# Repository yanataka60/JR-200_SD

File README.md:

# National JR-200にSD-CARDとのロード、セーブ機能

　JR-200でSD-CARDからcjr形式ファイルのロード、セーブ機能を実現するものです。

　CMTからの読み込み実行に数分掛かっていたゲームも数十秒で実行できます。

　接続は、JR-200本体後ろの拡張端子からフラットケーブルで接続して使います。

　なお、Arduino、ROMへ書き込むための機器が別途必要となります。

### 2025.2.26 PIOに6821を使ったRev2.1ではPIOアクセス時の画面ノイズが発生しないので6821版を正式版とし、8255版は8255フォルダに移動しました。なお、開発に使用した2台のJR-200では6821版、8255版ともに安定動作していますが、8255版は動作不安定であると報告された機体でも6821版は安定動作しているとの動作報告がありました。

## 回路図
　KiCadフォルダ内のJR-200_SD.pdfを参照してください。

[回路図](https://github.com/yanataka60/JR-200_SD/blob/main/Kicad/JR-200_SD.pdf)

## 部品
|番号|品名|数量|備考|
| ------------ | ------------ | ------------ | ------------ |
|J1|2x25ボックスヘッダ|1|共立エレショップ JS-1200R-50など、秋月電子通商 PH-2x40RGなどのピンヘッダでも代用可(注1)|
||J2、J3のいずれか|||
|J2|Micro_SD_Card_Kit|1|秋月電子通商 AE-microSD-LLCNV (注2) (注3)|
|J3|MicroSD Card Adapter|1|Arduino等に使われる5V電源に対応したもの (注3)|
|S1、S2|3Pスライドスイッチ又はピンヘッダ、ジャンパーピン|2|秋月電子通商 SS12D01G4など|
|U1、U3、U6|74LS04|3||
|U2、U4、U7|74LS30|3||
|U5|ROM 2764/27256/27512相当品|1||
|U8|6821|1|若松通商 HD46821P等|
|U9|Arduino_Pro_Mini_5V|1|Atmega328版を使用 168版は不可。(注4)|
|C2-C9|積層セラミックコンデンサ 0.1uF|8||
|C1|電解コンデンサ 16v100uF|1||
||50Pinフラットケーブル|1||
||ピンヘッダ|2Pin分|Arduino_Pro_MiniにはA4、A5用のピンヘッダが付いていないため別途調達が必要です 秋月電子通商 PH-1x40SGなど|
||ピンソケット(任意)|26Pin分|Arduino_Pro_Miniを取り外し可能としたい場合に調達します 秋月電子通商 FHU-1x42SGなど|

　　　注1)ピンヘッダで代用するときは、基板から若干浮かせてピンヘッダをハンダ付けするとフラットケーブをスムーズに抜き差しできます。

　　　注2)秋月電子通商　AE-microSD-LLCNVのJ1ジャンパはショートしてください。

　　　注3)J2又はJ3のどちらかを選択して取り付けてください。

### 　　注4)Arduino Pro MiniはA4、A5ピンも使っています。

### MicroSD Card Adapterを使う
　J3に取り付けます。

　MicroSD Card Adapterについているピンヘッダを除去してハンダ付けするのが一番確実ですが、J3の穴にMicroSD Card Adapterをぴったりと押しつけ、裏から多めにハンダを流し込むことでハンダ付けをする方法もあります。なお、この方法の時にはしっかりハンダ付けが出来たかテスターで導通を確認しておいた方が安心です。

　ハンダ付けに自信のない方はJ2の秋月電子通商　AE-microSD-LLCNVをお使いください。AE-microSD-LLCNVならパワーLED、アクセスLEDが付いています。

## ROMへの書込み
　ROMフォルダ内のSD.binをROMライター(TL866II Plus等)を使って2764、27256又は27512に書き込みます。

### ROMの相性
　開発中にAT28C64 15PCを使ったところ、正常に動作しないという現象がありました。

　AT28C64 15PCよりアクセスタイムが遅いROMを使用しても問題が発生しないため、単純にアクセスタイムの早いROMを使えばよいと言う訳でもないようです。

　入手性を鑑み、2764、27256、27512互換ROMを使えるようにしてあります。
#### 問題なし
|メーカー|品名|
| ------ | -- |
|ATMEL|AT28C64B-15PC|
|NEC|D27512J-2|
|ST|M2764A-25F1|
|ST|M27256-2F1|
|ST|M27C512-10F1|
|TOSHIBA|TMM2764D|
|TOSHIBA|TMM2764AD-20|
|Winbond|W27C512-45Z|

#### 問題あり
|メーカー|品名|備考|
| ------ | -- | -- |
|ATMEL|AT28C64-15PC|ほぼ誤動作|
|ATMEL|AT28C256-15PC|2764とはピン非互換|
|ATMEL|AT29C256-25PC|時々誤動作|

## Arduinoプログラム
　Arduino IDEを使ってArduinoフォルダのJR-200_SDフォルダ内JR-200.inoを書き込みます。

　SdFatライブラリを使用しているのでArduino IDEメニューのライブラリの管理からライブラリマネージャを立ち上げて「SdFat」をインストールしてください。

　「SdFat」で検索すれば見つかります。「SdFat」と「SdFat - Adafruit Fork」が見つかりますが「SdFat」のほうを使っています。

注)Arduinoを基板に直付けしている場合、Arduinoプログラムを書き込むときは、JR-200本体とは接続を外したうえで書き込んでください。

## 接続
　JR-200本体後ろの拡張端子からフラットケーブルで接続します。

.JPG)

#### 注)JR-200本体上面の塗装の下には伝導性の塗装(?)があるようで剥げかけている個所に接触するとショートの可能性があります。基板を本体上面に置くときには基板下面が本体と接触しないよう絶縁してください。

## SD-CARD
　出来ればSD規格のSDカードを用意してください。

　ArduinoのSdFatライブラリは、SD規格(最大2GB)、SDHC規格(2GB～32GB)に対応していますが、SDXC規格(32GB～2TB)には対応していません。

　また、SDHC規格のSDカードであっても相性により動作しないものがあるようです。

　FAT16又はFAT32が認識できます。NTFSは認識できません。

　ルートに置かれた拡張子が「.CJR」のCJR形式ファイルのみ認識できます。(CJR形式以外のファイル、フォルダも表示されますがLOADの対象になりません)

　ファイル名は「.CJR」を含めて31文字まで、ただし半角カタカナ、及び一部の記号はArduinoが認識しないので使えません。パソコンでファイル名を付けるときはアルファベット、数字および空白でファイル名をつけてください。

## CJR形式
　複数セクションが含まれるCJRファイルは読み込ませないでください。最初のセクションの読込が終了した後、Arduinoは次のセクションを送出しようとして待機状態となり、電源を入れ直すか、RESETするまで正常に動作しなくなります。

## 動作環境
　現在5.00と5.01での動作を確認しています。

## 使い方

### Launcherの起動
　MONコマンドでモニタに入り、G8000[CR]でLauncherが起動します。(Gは大文字)

　注)BASICからa=usr($8000)でも起動出来ますが、BASICプログラムをロードした後は、!コマンドで戻らずにBREAKキーで戻ってください。!コマンドで戻るとBASICプログラムが壊れます。

　コマンドプロンプトが「>」から「SD>」に変わり以下のコマンドが使えるようになります。

　~SDへのアクセス中に画面にノイズが出ますが、異常ではありません。ノイズが出ないようにする方法が不明なためそのままにしてあります。~(2025.2.20 PIOを6821にすることで解消されました。)

#### SDDIR[CR]又はSDDIR "文字列"[CR]
　SDDIR[CR]とするとSD-CARDルートディレクトリにあるファイルの一覧を表示します。

　SDDIR "文字列"[CR]とするとSD-CARDルートディレクトリにあるその文字列から始まるファイルの一覧を表示します。ダブルコーテーションはあっても無くても構いません。

　10件表示したところで指示待ちになるので打ち切るならRETURNを入力すると打ち切られ、Bキーで前の10件に戻ります。それ以外のキーで次の10件を表示します。

　LOADしたいファイルを見つけたら左端の数字のキーを押せばLOADされます。

　BASICプログラムか、機械語プログラムかは自動で判断します。

　表示される順番は、登録順となりファイル名アルファベッド順などのソートした順で表示することはできません。

#### LOAD "DOSファイル名"[CR]
　指定したDOSフィル名のプログラムをSD-CARDからLOADします。ダブルコーテーションはあっても無くても構いません。

　BASICプログラムか、機械語プログラムかは自動で判断し、どちらをLOADしているかメッセージに表示します。

　また、機械語プログラムのLOAD時には読み込み開始アドレス、読み込み終了アドレスも表示されます。

　ファイル名の最後の「.CJR」は有っても無くても構いません。

　例)

　　LOAD "TEST" -> DOSファイル名「TEST.CJR」を読み込みます。

　　LOAD "TEST.BAS" -> DOSファイル名「TEST.BAS.CJR」を読み込みます。

　　LOAD "TEST.BAS.CMT" -> DOSファイル名「TEST.BAS.CJR」を読み込みます。

#### MEXEC[CR]
　機械語プログラムをLOADした後、Gxxxx[CR]として機械語プログラムを実行する代わりに実行アドレスが読み込み開始アドレスと同じ場合にはMEXEC[CR]とすることで機械語プログラムを実行できます。

#### SAVE "DOSファイル名"[CR]
　BASICプログラムを指定したDOSフィル名でSD-CARDに上書きSAVEします。ダブルコーテーションはあっても無くても構いません。

　ファイル名の省略は出来ません。

　ファイル名の最後の「.CJR」は有っても無くても構いません。

　指定したDOSファイル名の最初の16文字がCJR形式の中に保存されるファイル名として使われます。

　BASICプログラムであることを識別するためDOSファイル名に「.BAS」を含ませることを推奨します。

　例)

　　SAVE "TEST" -> 「TEST.CJR」で保存される。

　　SAVE "TEST.BAS" -> 「TEST.BAS.CJR」で保存される。

#### MSAVE $xxxx,$yyyy,"DOSファイル名"[CR]
　16進数4桁で指定する$xxxxから$yyyyまでの機械語プログラムを指定したDOSフィル名でSD-CARDに上書きSAVEします。ダブルコーテーションはあっても無くても構いません。

　16進数4桁で指定するアドレスは$をつけてもつけなくても構いません。

　ファイル名の省略は出来ません。

　ファイル名の最後の「.CJR」は有っても無くても構いません。

　指定したDOSファイル名の最初の16文字がCJR形式の中に保存されるファイル名として使われます。

　機械語プログラムであることを識別するためDOSファイル名に「.BIN」を含ませることを推奨します。

　例)

　　MSAVE $E000,$FFFF,"TEST" -> 「TEST.CJR」で保存される。

　　MSAVE E000,FFFF,"TEST.BIN" -> 「TEST.BIN.CJR」で保存される。

#### G $xxxx[CR]
　16進数4桁で指定する$xxxxから始まるプログラムを実行します。

　16進数4桁で指定するアドレスは$をつけてもつけなくても構いません。

#### ![CR]
　JR-200のMONITORに戻ります。

　BASICからa=usr($8000)でLauncherを起動してBASICプログラムをロードした場合には、!コマンドでBASICに戻らないでください。BASICプログラムが破壊されます。

#### BREAKキー
　BASICに戻ります。

　JR-200のBREAKキーは割込み処理によりどんな時でもBASICに戻れるのですが、SDDIRを実行して10件表示したところで指示待ちの時には絶対に押さないでください。

　Arduinoが指示待ちのままになり、電源を再投入するか、リセットするまでSDは使えなくなります。

### BASICプログラム中から機械語プログラムをSDからLOADしたい場合
#### A=USR($8003):REM xxxxx
　A=USR($8003)の直後に書かれたREM文のコメント文字列(xxxxx)をファイル名として解釈してSDからLOADします。

　文字列をダブルコーテーションで括っても括らなくても構いません。また、事前にLauncherの起動も不要です。

　ただし、LOADするのは機械語プログラムのみにしてください。

　BASICプログラムをLOADするとBASICに復帰した時にBASICプログラムを破壊してしまい暴走します。(ダイレクトモードであっても破壊されます)

　例)

　　10 A=USR($8003):REM Demodata

## 操作上の注意
　SD-CARDにアクセスしていない時には電源が入ったままでもSD-CARDを抜くことが出来ます。

　再度SD-CARDを挿入した後、SDDIR、LOAD、SAVE等でSD-CARDに3回ほどアクセスすれば復旧します。

　ただし、SD-CARDの抜き差しは電源を切った状態で行うほうがより確実です。

## 謝辞
　基板の作成に当たり以下のデータを使わせていただきました。ありがとうございました。

　　Arduino Pro Mini

　　　https://github.com/g200kg/kicad-lib-arduino

　　AE-microSD-LLCNV

　　　https://github.com/kuninet/PC-8001-SD-8kRAM

## 追記
2025.1.27 部品に50Pinフラットケーブルを追加しました。

2025.1.29 コネクタの記述を修正しました。

2025.1.31 MSAVEのアドレス指定に$がついていた誤記を訂正しました。

2025.1.31 MSAVEのアドレス指定に$をつけてもつけなくてもよいことに修正。Gコマンドの記述が抜けていたので追加。JR-200_SD設置時の注意を追記。

2025.2.3 動作が不安定な時があるとの動作報告があったことを追記。

2025.2.20 PIOに6821を採用した6821版に移行した。

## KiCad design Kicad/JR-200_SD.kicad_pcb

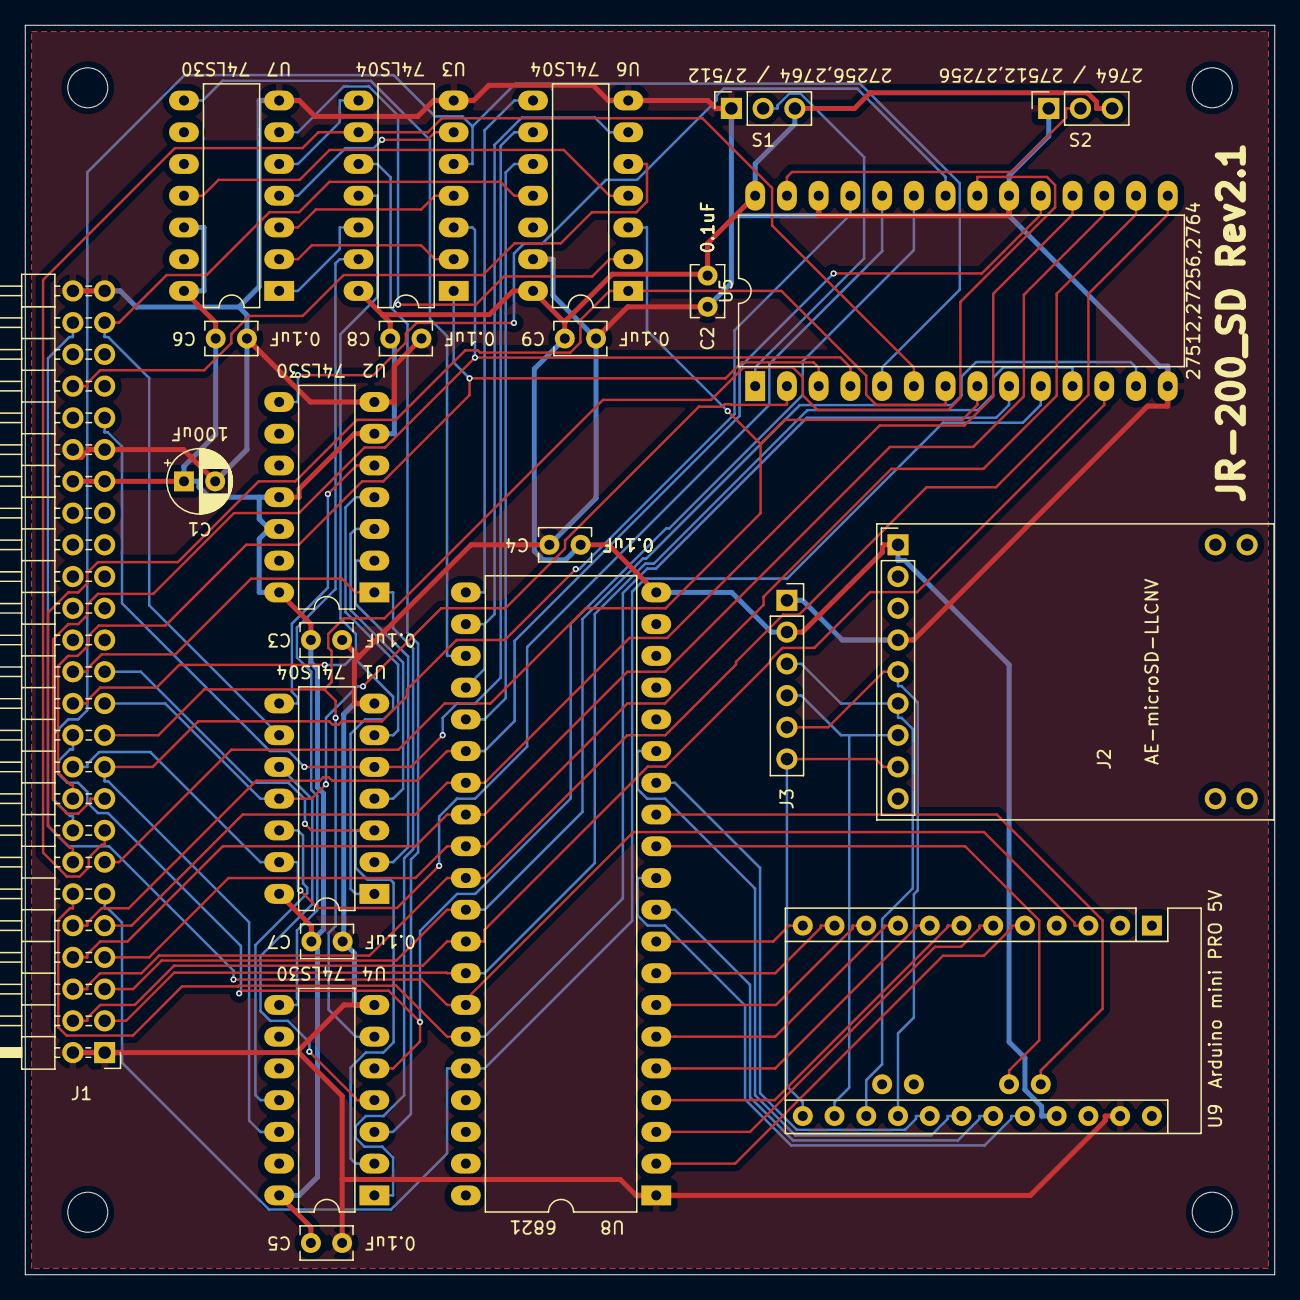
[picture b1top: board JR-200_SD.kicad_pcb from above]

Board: 2 copper layers, 100.0 x 100.0 mm, 27 parts (0 on the bottom side), 70 nets.

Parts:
C1: 100uF; CP_Radial_D5.0mm_P2.50mm
C2, C3, C4, C5, C6, C7, C8, C9: 0.1uF; C_Rect_L4.0mm_W2.5mm_P2.50mm
J1: Conn_02x25_Odd_Even; PinHeader_2x25_P2.54mm_Horizontal
J2: Micro_SD_Card_Kit; AE-microSD-LLCNV
J3: MicroSD Card Adapter; PinSocket_1x06_P2.54mm_Vertical
MH1, MH2, MH3, MH4: MountingHole_3.2mm_M3
S1: ROM 27512/27256 2764; PinSocket_1x03_P2.54mm_Vertical
S2: ROM 27512 27256/2764; PinSocket_1x03_P2.54mm_Vertical
U1, U3, U6: 74LS04; DIP-14_W7.62mm_LongPads
U2, U4, U7: 74LS30; DIP-14_W7.62mm_LongPads
U5: 27512; DIP-28_W15.24mm_LongPads
U8: 6821; DIP-40_W15.24mm_LongPads
U9: Arduino_Pro_Mini_5V; Arduino_Pro_Mini

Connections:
+5V: C1.1, C2.2, C3.1, C4.1, C5.1, C6.1, C7.1, C8.1, C9.1, J1.37, J1.38, J2.1, J3.2, S1.3, S2.3, U1.14, U2.6, U2.11, U2.12, U2.14, U3.14, U4.14, U5.28, U6.14, U7.12, U7.14, U8.20, U9.21
/A0: J1.11, U5.10, U8.36
/A1: J1.12, U5.9, U8.35
/A2: J1.13, U5.8, U6.3
/A3: J1.14, U5.7, U6.1
/A4: J1.15, U3.9, U5.6
/A5: J1.16, U3.5, U5.5
/A6: J1.17, U3.3, U5.4
/A7: J1.18, U3.1, U5.3
/A8: J1.19, U4.12, U5.25
/A9: J1.20, U1.13, U5.24
/A10: J1.21, U4.6, U5.21
/A11: J1.22, U4.5, U5.23
/A12: J1.23, U1.11, U5.2
/A13: J1.24, U1.1, U3.11
/A14: J1.25, U1.3, U4.2
/A15: J1.26, U2.1, U4.1
/CLOCK: J1.47, U1.9, U6.11
/CS: J2.8, J3.6, U9.13
/DB0: J1.3, U5.11, U8.33
/DB1: J1.4, U5.12, U8.32
/DB2: J1.5, U5.13, U8.31
/DB3: J1.6, U5.15, U8.30
/DB4: J1.7, U5.16, U8.29
/DB5: J1.8, U5.17, U8.28
/DB6: J1.9, U5.18, U8.27
/DB7: J1.10, U5.19, U8.26
/MISO: J2.6, J3.3, U9.15
/MOSI: J2.7, J3.4, U9.14
/SCK: J2.5, J3.5, U9.16
/~RD: J1.41, U1.5, U6.9
/~RESET: J1.48, U8.34, U9.3
/~VMA: J1.44, U6.5
GND: C1.2, C2.1, C3.2, C4.2, C5.2, C6.2, C7.2, C8.2, C9.2, J1.1, J1.2, J1.39, J1.40, J1.49, J1.50, J2.4, J3.1, S1.1, S2.1, U1.7, U2.7, U3.7, U4.7, U5.14, U5.20, U5.26, U6.7, U6.13, U7.7, U8.1, U9.23
unnamed: S1.2, U5.1
unnamed: S2.2, U5.27
unnamed: U1.2, U2.2
unnamed: U1.4, U2.3
unnamed: U1.6, U2.4
unnamed: U1.8, U2.5
unnamed: U1.10, U4.4
unnamed: U1.12, U4.11
unnamed: U2.8, U5.22
unnamed: U3.2, U7.2
unnamed: U3.4, U7.3
unnamed: U3.6, U7.4
unnamed: U3.8, U7.5
unnamed: U3.10, U4.3
unnamed: U3.12, U7.1
unnamed: U3.13, U4.8
unnamed: U6.2, U7.6
unnamed: U6.4, U7.11
unnamed: U6.6, U8.22, U8.24
unnamed: U6.8, U8.21
unnamed: U6.10, U8.25
unnamed: U7.8, U8.23
unnamed: U8.2, U9.5
unnamed: U8.3, U9.6
unnamed: U8.4, U9.7
unnamed: U8.5, U9.8
unnamed: U8.6, U9.9
unnamed: U8.7, U9.10
unnamed: U8.8, U9.11
unnamed: U8.9, U9.12
unnamed: U8.10, U9.19
unnamed: U8.11, U9.20
unnamed: U8.12, U9.A4
unnamed: U8.13, U9.A5
unnamed: U8.14, U9.17
unnamed: U8.15, U9.18
